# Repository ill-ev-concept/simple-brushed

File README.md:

# Ethan Brushed Simple

This is the simple version of the brushed motor controller for EV3, my current documentation can be found [here](https://docs.google.com/document/d/1gfZzmsv_RstbJ-Lk0RfqkkH_zSeoGgdf7qZ41NG-Wzg/edit?usp=sharing)

Additionally, the code can be found <a href = "https://gitlab.engr.illinois.edu/ev-concept/software2022-23/embedded/brushed-motors/brushed-motor-simple-26-27">here</a>

Currently works on the bench with minor modifications and problems:

 - Footprint for mosfet is reversed, so bodge wire was used to swap trace for gate pin
 - Buck converter possibly having some issues, previously worked in testing, but now doesnt function so it is being bypassed
 - Gate driver IC seems to pull down the STMs PWM signal to 2 volts peak, which is just enough for it to detect, but 3.3v is prefered

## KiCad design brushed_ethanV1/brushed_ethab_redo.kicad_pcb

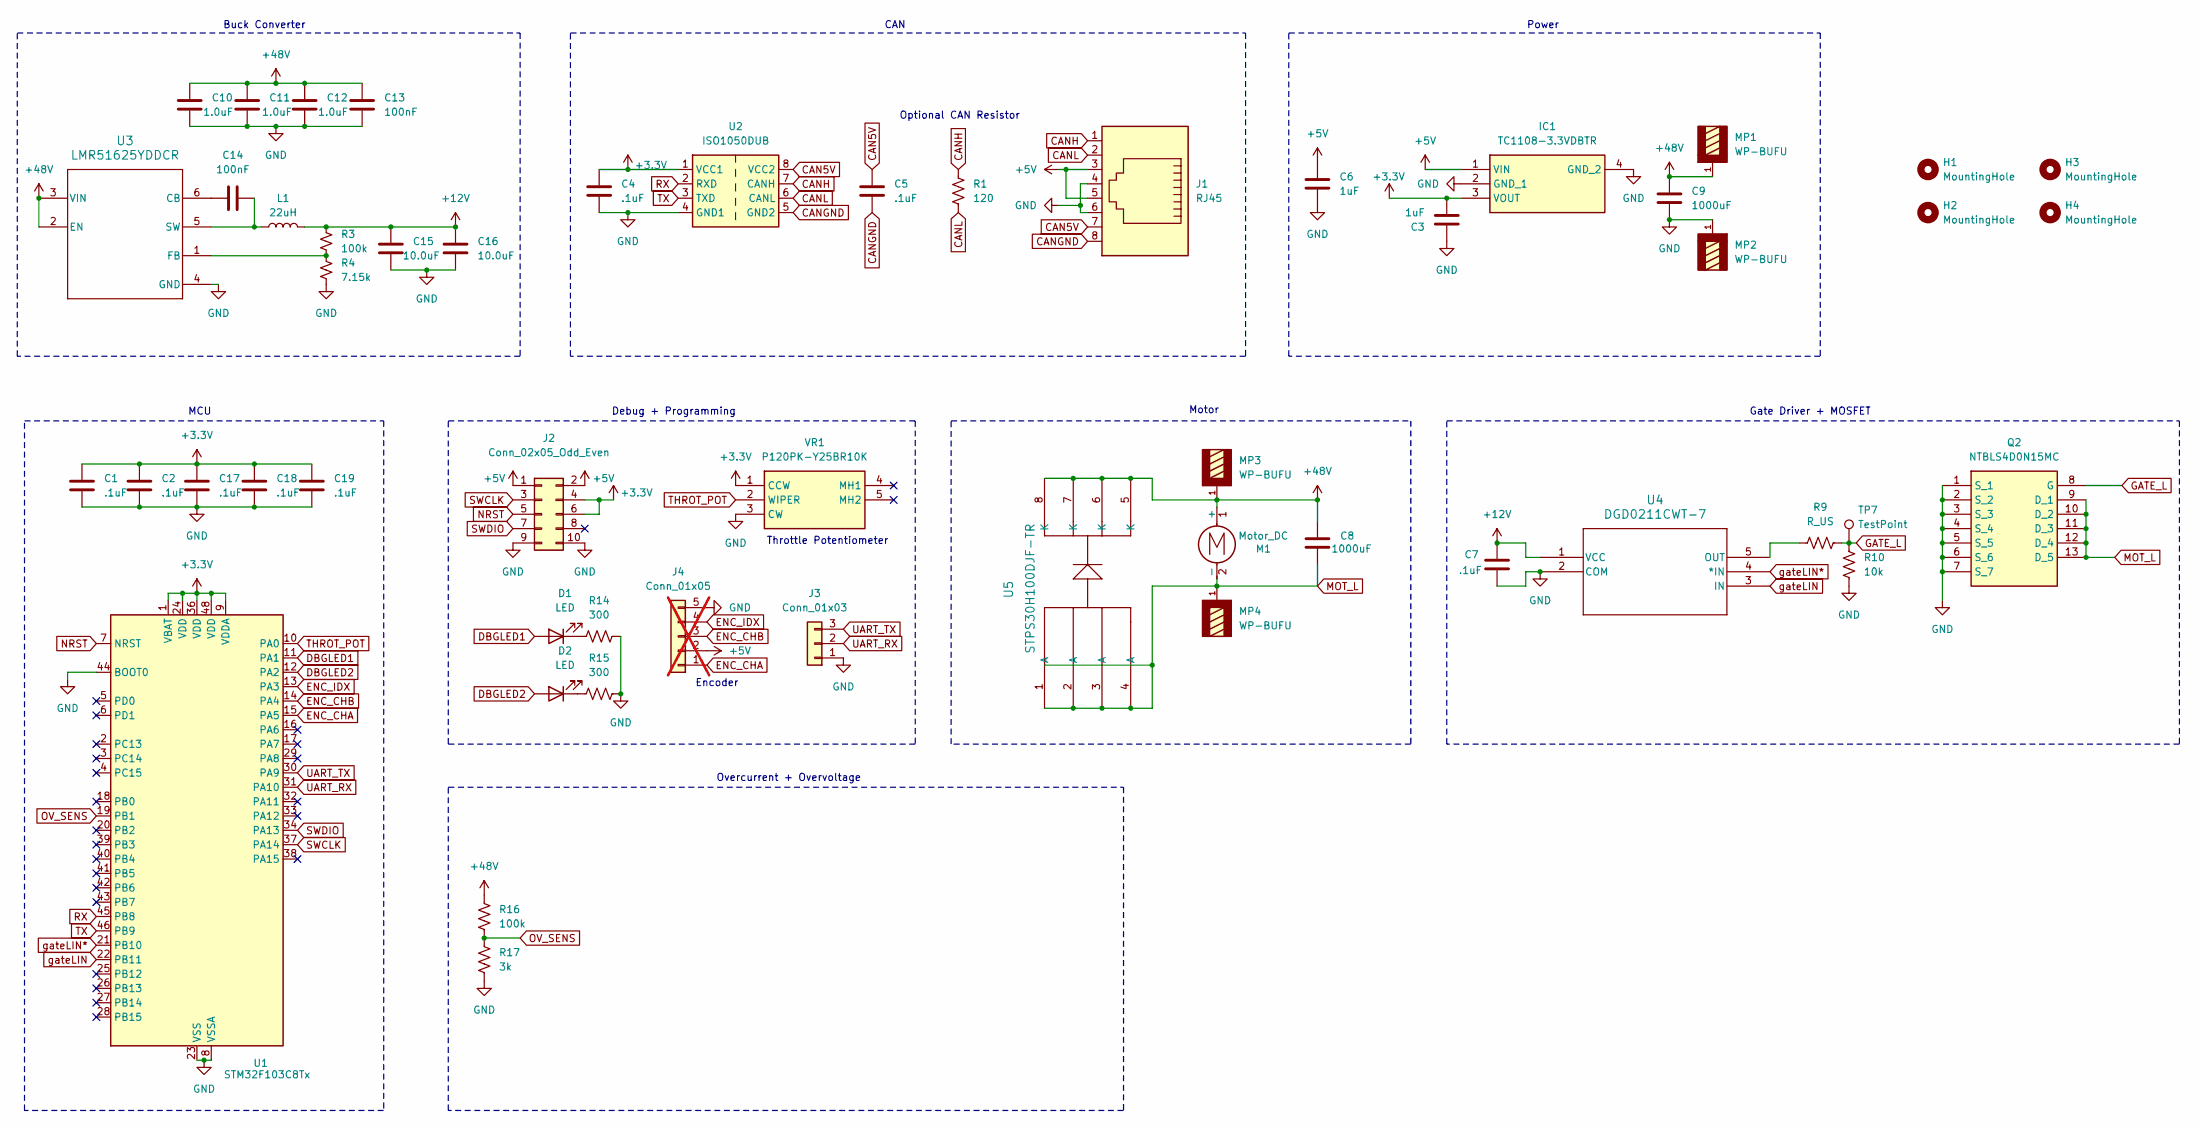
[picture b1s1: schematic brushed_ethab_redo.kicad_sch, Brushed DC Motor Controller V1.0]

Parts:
C1, C2, C4, C5, C7, C17, C18, C19: .1uF; C_0805_2012Metric_Pad1.18x1.45mm_HandSolder
C3, C6: 1uF; C_0805_2012Metric_Pad1.18x1.45mm_HandSolder
C8, C9: 1000uF; CP_Radial_D18.0mm_P7.50mm
C10, C11, C12: 1.0uF; C_1206_3216Metric
C13: 100nF; C_0603_1608Metric_Pad1.08x0.95mm_HandSolder
C14: 100nF; C_0402_1005Metric_Pad0.74x0.62mm_HandSolder
C15, C16: 10.0uF; C_1210_3225Metric
D1, D2: LED; LED_0805_2012Metric_Pad1.15x1.40mm_HandSolder
H1, H2, H3, H4: MountingHole; MountingHole_4.3mm_M4
IC1: TC1108-3.3VDBTR; SOT230P700X180-4N; Manufacturer_Part_Number TC1108-3.3VDBTR; Mouser Part Number 579-TC1108-3.3VDBTR
J1: RJ45; RJ45_Amphenol_54602-x08_Horizontal
J2: Conn_02x05_Odd_Even; PinSocket_2x05_P2.54mm_Vertical
J3: Conn_01x03; PinSocket_1x03_P2.54mm_Vertical
J4: Conn_01x05; PinSocket_1x05_P2.54mm_Vertical; not fitted
L1: 22uH; L_Bourns_SRR1208_12.7x12.7mm
M1: Motor_DC
MP1, MP2, MP3, MP4: WP-BUFU; WP-BUFU_7461097; DigiKey_Part_Number 732-3217-ND
Q2: NTBLS4D0N15MC; Manufacturer_Part_Number NTBLS4D0N15MC; Mouser Part Number 863-NTBLS4D0N15MC
R1: 120; R_0805_2012Metric_Pad1.20x1.40mm_HandSolder
R3: 100k; R_0402_1005Metric_Pad0.72x0.64mm_HandSolder
R4: 7.15k; R_0603_1608Metric_Pad0.98x0.95mm_HandSolder
R9: R_US; R_0805_2012Metric_Pad1.20x1.40mm_HandSolder
R10: 10k; R_0805_2012Metric_Pad1.20x1.40mm_HandSolder
R14, R15: 300; R_0805_2012Metric_Pad1.20x1.40mm_HandSolder
R16: 100k; R_0805_2012Metric_Pad1.20x1.40mm_HandSolder
R17: 3k; R_0805_2012Metric_Pad1.20x1.40mm_HandSolder
TP7: TestPoint; TestPoint_Pad_D1.0mm
U1: STM32F103C8Tx; LQFP-48_7x7mm_P0.5mm
U2: ISO1050DUB; SOP-8_6.62x9.15mm_P2.54mm
U3: LMR51625YDDCR; BUCK_LMR51625YDDCR
U4: DGD0211CWT-7; TSOT25-TH_DIO
U5: STPS30H100DJF-TR; MOSFET_100DJF-TR_STM
VR1: P120PK-Y25BR10K; P120PKY25BR10K; Manufacturer_Part_Number P120PK-Y25BR10K; Mouser Part Number 858-P120PKY25BR10K

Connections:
+3.3V: C1.1, C2.1, C3.2, C4.1, C17.1, C18.1, C19.1, IC1.3 (VOUT), J2.4, J2.6, U1.1 (VBAT), U1.9 (VDDA), U1.24 (VDD), U1.36 (VDD), U1.48 (VDD), U2.1 (VCC1), VR1.1 (CCW)
+5V: C6.1, IC1.1 (VIN), J1.3, J1.5, J2.1, J2.2, J4.2
+12V: C7.1, C15.1, C16.1, L1.2, R3.1, U4.1 (VCC)
+48V: C8.1, C9.1, C10.1, C11.1, C12.1, C13.1, M1.1 (+), MP1.1, MP1.2, MP1.3, MP1.4, MP1.5, MP1.6, MP1.7, MP1.8, MP1.9, MP1.10, MP1.11, MP1.12, MP1.13, MP1.14, MP1.15, MP1.16, MP3.1, MP3.2, MP3.3, MP3.4, MP3.5, MP3.6, MP3.7, MP3.8, MP3.9, MP3.10, MP3.11, MP3.12, MP3.13, MP3.14, MP3.15, MP3.16, R16.2, U3.2 (EN), U3.3 (VIN), U5.5 (K), U5.6 (K), U5.7 (K), U5.8 (K)
CAN5V: C5.1, J1.7, U2.8 (VCC2)
CANGND: C5.2, J1.8, U2.5 (GND2)
CANH: J1.1, R1.1, U2.7 (CANH)
CANL: J1.2, R1.2, U2.6 (CANL)
DBGLED1: D1.2 (A), U1.11 (PA1)
DBGLED2: D2.2 (A), U1.12 (PA2)
ENC_CHA: J4.1, U1.15 (PA5)
ENC_CHB: J4.3, U1.14 (PA4)
ENC_IDX: J4.4, U1.13 (PA3)
GATE_L: Q2.8 (G), R9.2, R10.2, TP7.1 (1_1)
GND: C1.2, C2.2, C3.1, C4.2, C6.2, C7.2, C9.2, C10.2, C11.2, C12.2, C13.2, C15.2, C16.2, C17.2, C18.2, C19.2, IC1.2 (GND_1), IC1.4 (GND_2), J1.4, J1.6, J2.9, J2.10, J3.1, J4.5, MP2.1, MP2.2, MP2.3, MP2.4, MP2.5, MP2.6, MP2.7, MP2.8, MP2.9, MP2.10, MP2.11, MP2.12, MP2.13, MP2.14, MP2.15, MP2.16, Q2.1 (S_1), Q2.2 (S_2), Q2.3 (S_3), Q2.4 (S_4), Q2.5 (S_5), Q2.6 (S_6), Q2.7 (S_7), R4.2, R10.1, R14.2, R15.2, R17.1, U1.8 (VSSA), U1.23 (VSS), U1.35 (VSS), U1.44 (BOOT0), U1.47 (VSS), U2.4 (GND1), U3.4 (GND), U4.2 (COM), VR1.3 (CW)
MOT_L: C8.2, M1.2 (-), MP4.1, MP4.2, MP4.3, MP4.4, MP4.5, MP4.6, MP4.7, MP4.8, MP4.9, MP4.10, MP4.11, MP4.12, MP4.13, MP4.14, MP4.15, MP4.16, Q2.9 (D_1), Q2.10 (D_2), Q2.11 (D_3), Q2.12 (D_4), Q2.13 (D_5), U5.1 (A), U5.2 (A), U5.3 (A), U5.4 (A)
NRST: J2.5, U1.7 (NRST)
unnamed: D1.1 (K), R14.1
unnamed: D2.1 (K), R15.1
unnamed: C14.1, U3.6 (CB)
unnamed: R3.2, R4.1, U3.1 (FB)
unnamed: C14.2, L1.1, U3.5 (SW)
unnamed: R9.1, U4.5 (OUT)
OV_SENS: R16.1, R17.2, U1.19 (PB1)
RX: U1.45 (PB8), U2.2 (RXD)
SWCLK: J2.3, U1.37 (PA14)
SWDIO: J2.7, U1.34 (PA13)
THROT_POT: U1.10 (PA0), VR1.2 (WIPER)
TX: U1.46 (PB9), U2.3 (TXD)
UART_RX: J3.2, U1.31 (PA10)
UART_TX: J3.3, U1.30 (PA9)
gateLIN: U1.22 (PB11), U4.3 (IN)
gateLIN*: U1.21 (PB10), U4.4 (*IN)

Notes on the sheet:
Buck Converter
Power
Encoder
Optional CAN Resistor
Throttle Potentiometer
Motor
MCU
CAN
Gate Driver + MOSFET
Overcurrent + Overvoltage
Debug + Programming

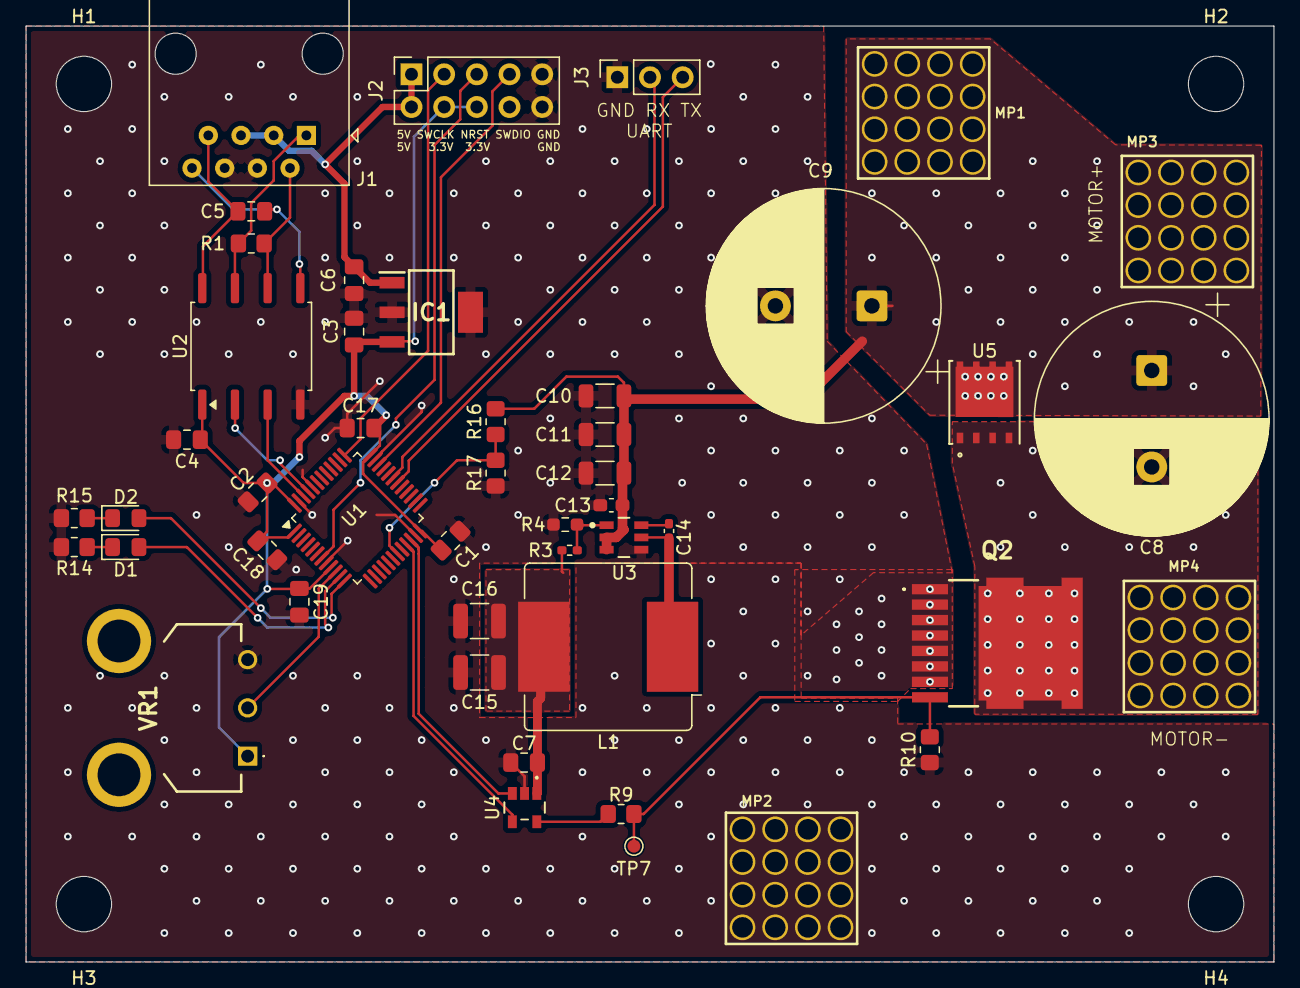
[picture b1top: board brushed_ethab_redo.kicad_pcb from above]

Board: 2 copper layers, 97.0 x 72.8 mm, 51 parts (0 on the bottom side), 30 nets.

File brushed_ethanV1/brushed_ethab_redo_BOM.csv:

Reference,Qty,Value,DNP,Exclude from BOM,Exclude from Board,Footprint,Datasheet,,,,,,,,,,ordered?,do I have in bring home box?,
"C1,C2,C4,C5,C7,C17,C18,C19",8,.1uF,,,,Capacitor_SMD:C_0805_2012Metric_Pad1.18x1.45mm_HandSolder,,,,,,,,,,,y,y but they are 0603,
"C3,C6",2,1uF,,,,Capacitor_SMD:C_0805_2012Metric_Pad1.18x1.45mm_HandSolder,,,,,,,,,,,y,y,
"C8,C9",2,C,,,,Capacitor_THT:CP_Radial_D18.0mm_P7.50mm,,,,,,,,,,,y,y,
"C10,C11,C12",3,1.0uF,,,,Capacitor_SMD:C_1206_3216Metric,,,,,,,,,,,y,y,
C13,1,100nF,,,,Capacitor_SMD:C_0603_1608Metric_Pad1.08x0.95mm_HandSolder,,,,,,,,,,,y,y,
C14,1,100nF,,,,Capacitor_SMD:C_0402_1005Metric_Pad0.74x0.62mm_HandSolder,,,,,,,,,,,y,y,
"C15,C16",2,10.0uF,,,,Capacitor_SMD:C_1210_3225Metric,,,,,,,,,,,y,y,
"D1,D2",2,LED,,,,LED_SMD:LED_0805_2012Metric_Pad1.15x1.40mm_HandSolder,,,,,,,,,,,y,y,
IC1,1,TC1108-3.3VDBTR,,,,SamacSys_Parts:SOT230P700X180-4N,http://ww1.microchip.com/downloads/en/DeviceDoc/21357C.pdf,,,,,,,,,,y,y,
J1,1,RJ45,,,,Connector_RJ:RJ45_Amphenol_54602-x08_Horizontal,,,,,,,,,,,alr have,y,
J2,1,Conn_02x05_Odd_Even,,,,Connector_PinSocket_2.54mm:PinSocket_2x05_P2.54mm_Vertical,,,,,,,,,,,alr have,y,
J3,1,Conn_01x03,,,,Connector_PinSocket_2.54mm:PinSocket_1x03_P2.54mm_Vertical,,,,,,,,,,,alr have,y,
J4,1,Conn_01x05,DNP,,Excluded from board,Connector_PinSocket_2.54mm:PinSocket_1x05_P2.54mm_Vertical,,,,,,,,,,,,,
L1,1,22uH,,,,Inductor_SMD:L_Bourns_SRR1208_12.7x12.7mm,,,,,,,,,,,y,y,
M1,1,Motor_DC,,,Excluded from board,,,,,,,,,,,,,,
"MP1,MP2,MP3,MP4",4,WP-BUFU,,,,WP-BUFU:WP-BUFU_7461097,,,,,,,,,,,y,y,
Q2,1,NTBLS4D0N15MC,,,,SamacSys_Parts:NTBLS4D0N15MC,https://www.onsemi.com/pub/Collateral/NTBLS4D0N15MC-D.PDF,,,,,,,,,,y,y,
R1,1,120,,,,Resistor_SMD:R_0805_2012Metric_Pad1.20x1.40mm_HandSolder,,,,,,,,,,,,,
R3,1,100k,,,,Resistor_SMD:R_0402_1005Metric_Pad0.72x0.64mm_HandSolder,,,,,,,,,,,y,y,
R4,1,7.15k,,,,Resistor_SMD:R_0603_1608Metric_Pad0.98x0.95mm_HandSolder,,,,,,,,,,,y,y,
R9,1,10,,,,Resistor_SMD:R_0805_2012Metric_Pad1.20x1.40mm_HandSolder,,10ohm,,,,,,,,,y,y,
R10,1,10k,,,,Resistor_SMD:R_0805_2012Metric_Pad1.20x1.40mm_HandSolder,,,,,,,,,,,y,y,
"R14,R15",2,300,,,,Resistor_SMD:R_0805_2012Metric_Pad1.20x1.40mm_HandSolder,,,,,,,,,,,alr have,,ig not bringing these home
R16,1,100k,,,,Resistor_SMD:R_0805_2012Metric_Pad1.20x1.40mm_HandSolder,,,,,,,,,,,y,y,
R17,1,3k,,,,Resistor_SMD:R_0805_2012Metric_Pad1.20x1.40mm_HandSolder,,,,,,,,,,,y,y,
TP7,1,TestPoint,,,,TestPoint:TestPoint_Pad_D1.0mm,,,,,,,,,,,,,
U1,1,STM32F103C8Tx,,,,Package_QFP:LQFP-48_7x7mm_P0.5mm,https://www.st.com/resource/en/datasheet/stm32f103c8.pdf,,,,,,,,,,y,y,
U2,1,ISO1050DUB,,,,Package_SO:SOP-8_6.62x9.15mm_P2.54mm,http://www.ti.com/lit/ds/symlink/iso1050.pdf,,,,,,,,,,alr have,y,
U3,1,LMR51625YDDCR,,,,BrushedDC2:BUCK_LMR51625YDDCR,https://www.ti.com/lit/gpn/lmr51625,,,,,,,,,,y,y,
U4,1,DGD0211CWT-7,,,,gatedriver:TSOT25-TH_DIO,DGD0211CWT-7,,,,,,,,,,y at home,,
U5,1,STPS30H100DJF-TR,,,,BrushedDC2:MOSFET_100DJF-TR_STM,https://www.st.com/resource/en/datasheet/stps30h100djf.pdf,,,,,,,,,,y,y,
VR1,1,P120PK-Y25BR10K,,,,SamacSys_Parts:P120PKY25BR10K,https://www.ttelectronics.com/TTElectronics/media/ProductFil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,,,,,,,,,,y,y,
